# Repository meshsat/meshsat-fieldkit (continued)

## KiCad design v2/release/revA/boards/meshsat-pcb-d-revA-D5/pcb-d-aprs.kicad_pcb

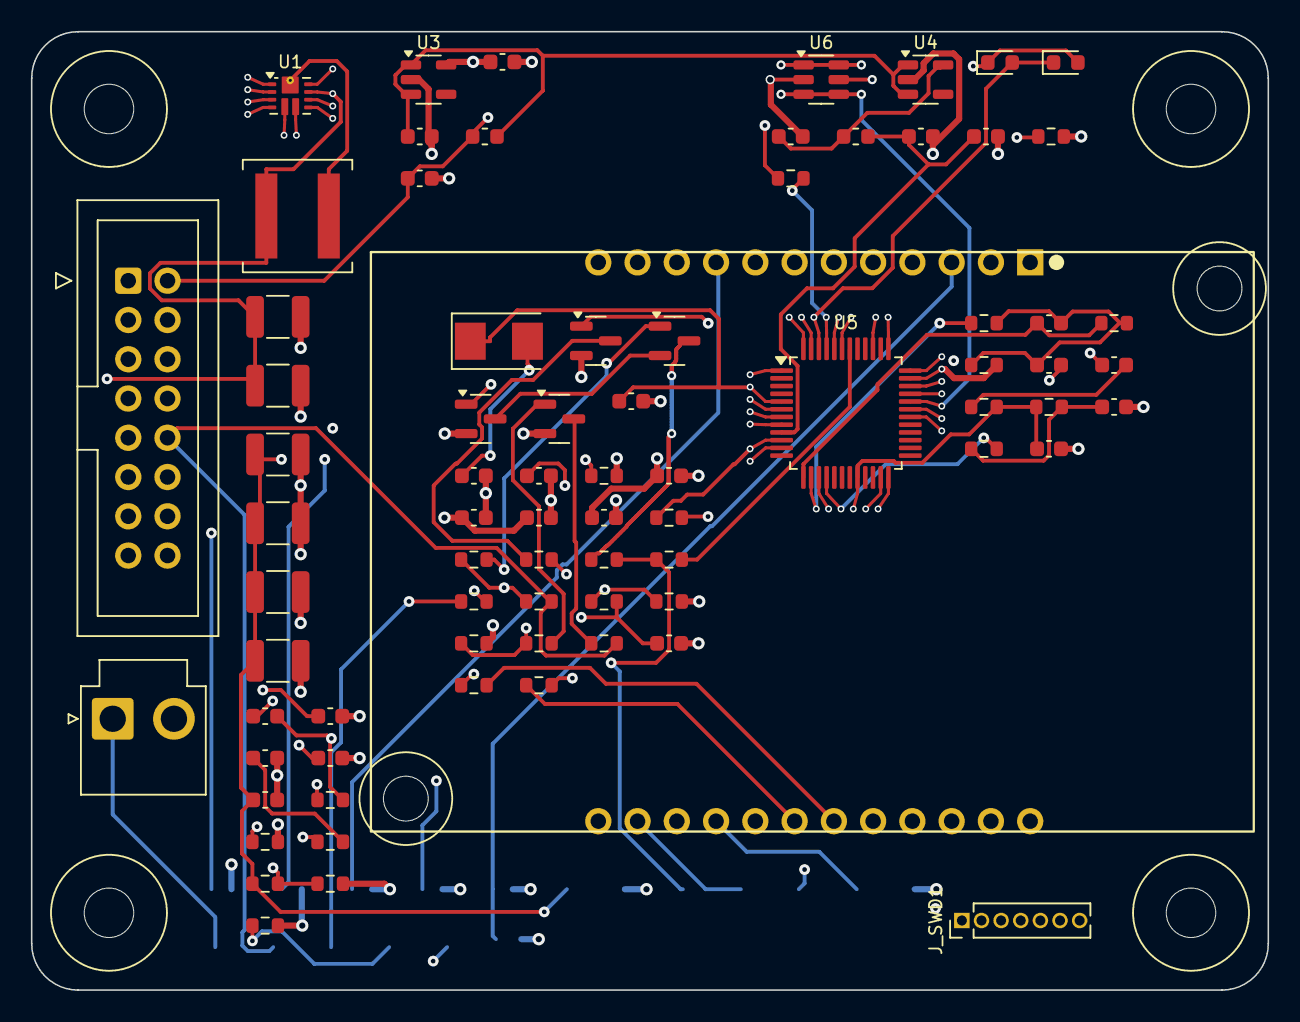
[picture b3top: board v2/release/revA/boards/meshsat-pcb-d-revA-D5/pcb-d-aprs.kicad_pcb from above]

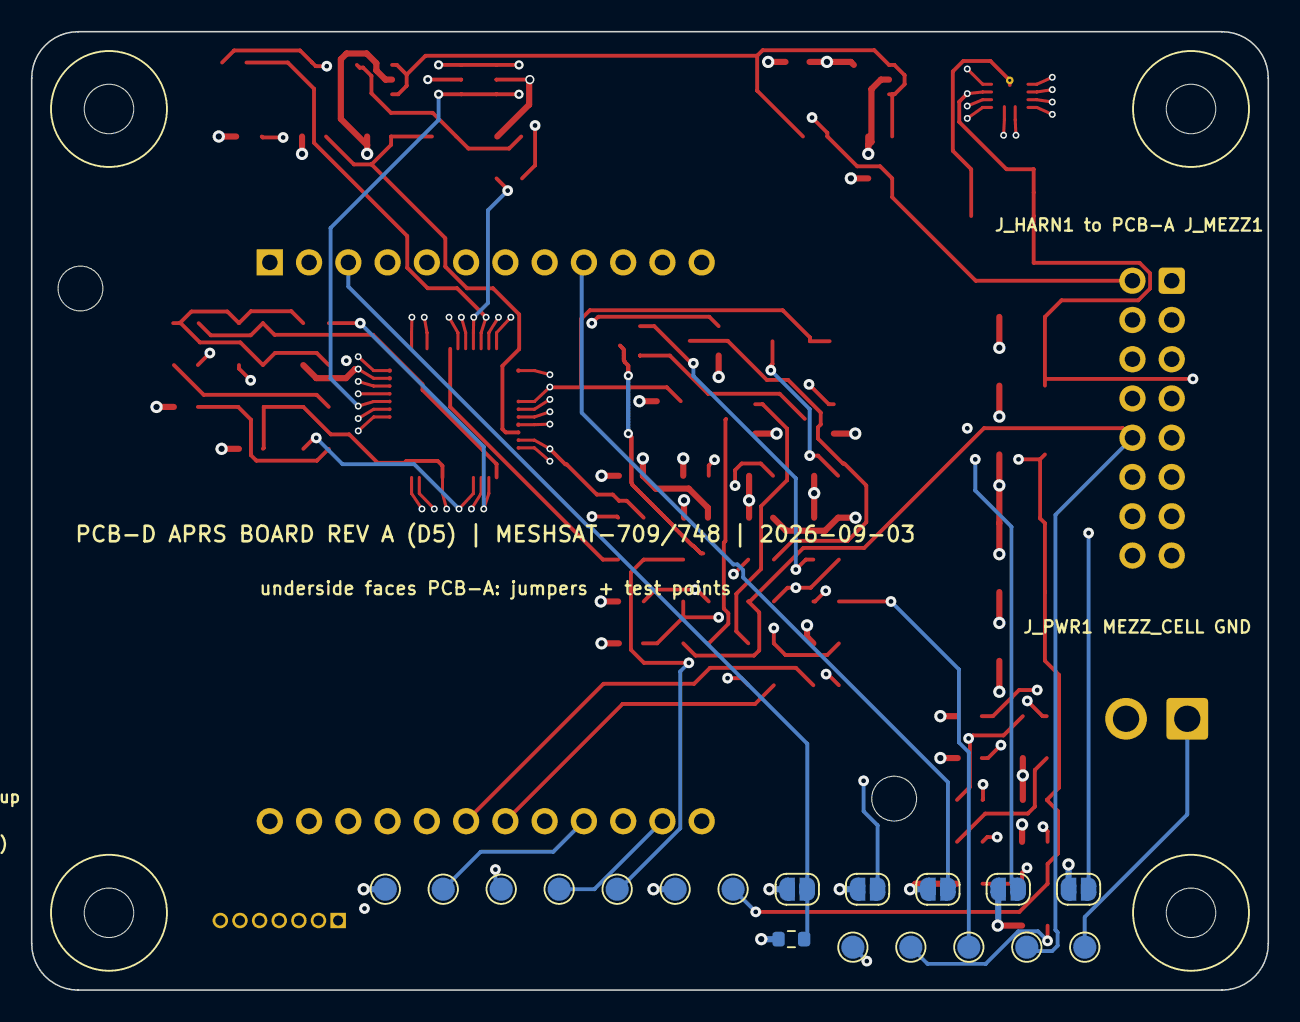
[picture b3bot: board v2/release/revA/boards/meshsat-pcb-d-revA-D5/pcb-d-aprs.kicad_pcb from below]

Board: 4 copper layers, 80.0 x 62.0 mm, 100 parts (18 on the bottom side), 64 nets.

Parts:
C1, C2: 22p NP0; C_0603_1608Metric
C4, C5, C6, C7, C10, C13, C14, C31: 4.7u; C_0603_1608Metric
C8, C9, C12, C15, C16, C17, C18, C25, C32: 100n; C_0603_1608Metric
C11: 4.7n NP0; C_0603_1608Metric
C20, C30: 100n 25V; C_0603_1608Metric
C21: 1u; C_0603_1608Metric
C22: 4.7n; C_0603_1608Metric
C23, C24: 22u 10V X7R 1210; C_1210_3225Metric
C26, C27, C28, C29: 22u 25V X7R 1210; C_1210_3225Metric
D1: green; LED_0603_1608Metric
D2: red; LED_0603_1608Metric
FB1, FB2: 600R@100MHz; L_0603_1608Metric
H1, H2, H3, H4: M3 standoff to PCB-A; MountingHole_3.2mm_M3
JP1: channel bit CH8 to GND (open = default); SolderJumper-2_P1.3mm_Open_RoundedPad1.0x1.5mm
JP2: channel bit CH4 to GND (open = default); SolderJumper-2_P1.3mm_Open_RoundedPad1.0x1.5mm
JP3: channel bit CH2 to GND (open = default); SolderJumper-2_P1.3mm_Open_RoundedPad1.0x1.5mm
JP4: channel bit CH1 to GND (open = default); SolderJumper-2_P1.3mm_Open_RoundedPad1.0x1.5mm
JP5: CS to GND = module sleep; SolderJumper-2_P1.3mm_Open_RoundedPad1.0x1.5mm
J_HARN1: harness to PCB-A J_MEZZ1 (IDC 2x8); UART pair and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; IDC-Header_2x08_P2.54mm_Vertical
J_PWR1: cell node from PCB-A J_MEZZ_PWR (JST-VH); JST_VH_B2P-VH_1x02_P3.96mm_Vertical
J_SWD1: SWD/DFU 1.27 mm: BOOT0 SWO NRST SWDIO GND SWCLK 3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; PinHeader_1x07_P1.27mm_Vertical
L1: 1.5uH XAL6030-152MEB (Isat 12 A, 5.6 mOhm); L_Coilcraft_XAL6030-XXX
Q1: BC847 (PTT2, spare); SOT-23
Q2: BC847 (PTT to the module); SOT-23
Q3: 2N7002 (EMCON inhibit in Q2 emitter); SOT-23
Q4: BC857 (TR mirror from RADIO_PTT); SOT-23
R1, R4, R10, R11, R18, R19: 1.5k; R_0603_1608Metric
R2: 4.7k; R_0603_1608Metric
R3, R8, R9, R15, R17, R41: 100R; R_0603_1608Metric
R5, R14, R16: 5.1k; R_0603_1608Metric
R12, R13: 22R; R_0603_1608Metric
R22: DNP 100R (mirror now via Q4); R_0603_1608Metric
R30: 301k 1% (500 kHz); R_0603_1608Metric
R31: 100k 1% (ILIM 10 A peak, 9 A min); R_0603_1608Metric
R32: 17.4k; R_0603_1608Metric
R33: 105k 1%; R_0603_1608Metric
R34: 20k 1%; R_0603_1608Metric
R35, R38, R39: 100k; R_0603_1608Metric
R36, R40: 10k; R_0603_1608Metric
R37: 1k; R_0603_1608Metric
TP1: V8; TestPoint_Pad_D1.5mm
TP2: GND; TestPoint_Pad_D1.5mm
TP3: RADIO_PTT; TestPoint_Pad_D1.5mm
TP4: RADIO_MIC; TestPoint_Pad_D1.5mm
TP5: RADIO_SPK; TestPoint_Pad_D1.5mm
TP6: SPKEN; TestPoint_Pad_D1.5mm
TP7: +3V3; TestPoint_Pad_D1.5mm
TP8: VIN_CELL; TestPoint_Pad_D1.5mm
TP9: TR_APRS; TestPoint_Pad_D1.5mm
TP10: RADIO_PTT2; TestPoint_Pad_D1.5mm
TP11: MEZZ_EN; TestPoint_Pad_D1.5mm
TP12: TX_INHIBIT_n; TestPoint_Pad_D1.5mm
U1: TPS61089 boost 7.6 V / 2 A; Texas_VQFN-RNR0011A-11
U2: DNP bench: DMR858M 5 W UHF module on 2 x 1x12 2.5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; DMR858M
U3: AP2112K-3.3 digital; SOT-23-5
U4: AP2112K-3.3 analog; SOT-23-5
U5: STM32F302CBT6 128 KB (AIOC firmware 1.4.1 is 128,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; LQFP-48_7x7mm_P0.5mm
U6: USBLC6-2SC6; SOT-23-6
Y1: 8MHz 20pF 5032; Crystal_SMD_5032-2Pin_5.0x3.2mm

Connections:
+3V3: C4.1, C7.1, C8.1, C17.1, C18.1, J_SWD1.7, Q4.2, R1.2, R36.2, R38.2, R39.2, TP7.1, U3.5, U5.1, U5.24, U5.36, U5.48
/+3.3VA: C9.1, C10.1, FB1.2, U5.9
/+5V_USB: C31.1, FB2.1, J_HARN1.2, U6.5
/ADC_BIAS: R3.2, U5.16
/AFIN: C11.1, R5.2, R16.1, U5.15, U5.20
/AFOUT: R2.1, U5.14
/BIAS_NODE: C16.1, R3.1, R16.2
/BOOT: C20.1, U1.10
/BOOT0: J_SWD1.1, R14.1, U5.44
/BST_VCC: C21.1, U1.2
/CH1: JP4.1, U2.10
/CH2: JP3.1, U2.9
/CH4: JP2.1, U2.8
/CH8: JP1.1, U2.7
/COMP: R32.1, U1.4
/COMPC: C22.1, R32.2
/CS: JP5.1, R36.1, U2.3
/DAC_ATTEN: C12.1, R17.1, U5.13
/FB8: R33.2, R34.1, U1.3
/FSW: R30.1, U1.1
/ILIM: R31.1, U1.8
/IN1: R19.2, U5.42
/IN2: R18.2, U5.43
/LDO_A: C5.1, FB1.1, U4.5
/LED_A: D1.2, D2.1, U5.46
/LED_K: D1.1, D2.2, R15.1
/LED_R: R15.2, U5.45
/MEZZ_EN: J_HARN1.11, R35.1, TP11.1, U1.7
/MIC_NODE: C12.2, C13.1, R2.2, R4.1, R17.2
/NRST: C15.1, J_SWD1.3, U5.7
/OSCIN: C1.1, U5.5, Y1.1
/OSCOUT: C2.1, U5.6, Y1.2
/OUT1: R11.1, R22.1, U5.11
/OUT2: R10.1, U5.10
/Q1_B: Q1.1, R10.2
/Q1_C: Q1.3, R12.1
/Q2_B: Q2.1, R11.2
/Q2_C: Q2.3, R13.1
/Q2_E: Q2.2, Q3.3
/Q3_G: C32.1, Q3.1, R37.2
/Q4_B: Q4.1, R40.2
/Q4_C: Q4.3, R41.1
/RADIO_MIC: C13.2, TP4.1, U2.14
/RADIO_PTT: R13.2, R19.1, R39.1, R40.1, TP3.1, U2.5
/RADIO_PTT2: R12.2, R18.1, TP10.1
/RADIO_RX: R8.2, U2.19
/RADIO_SPK: C14.1, TP5.1, U2.6
/RADIO_TX: R9.1, U2.18
/SPKEN: J_HARN1.14, TP6.1, U2.16
/SPK_NODE: C14.2, R5.1
/SW: C20.2, L1.2, R30.2, U1.11
/SWCLK: J_SWD1.6, U5.37
/SWDIO: J_SWD1.4, U5.34
/SWO: J_SWD1.2, U5.39
/TR_APRS: J_HARN1.10, R22.2, R41.2, TP9.1
/TX_INHIBIT_n: J_HARN1.15, R37.1, R38.1, TP12.1
/USART_RX: R9.2, U5.31
/USART_TX: R8.1, U5.30
/USB_DM: J_HARN1.4, U5.32, U6.3, U6.4
/USB_DP: J_HARN1.3, R1.1, U5.33, U6.1, U6.6
/V8: C26.1, C27.1, C28.1, C29.1, C30.1, R33.1, TP1.1, U1.6, U2.1
/VIN_CELL: C23.1, C24.1, C25.1, J_PWR1.1, L1.1, TP8.1, U1.9
/VIN_LDO: C6.1, FB2.2, U3.1, U3.3, U4.1, U4.3
GND: C1.2, C2.2, C4.2, C5.2, C6.2, C7.2, C8.2, C9.2, C10.2, C11.2, C15.2, C16.2, C17.2, C18.2, C21.2, C22.2, C23.2, C24.2, C25.2, C26.2, C27.2, C28.2, C29.2, C30.2, C31.2, C32.2, JP1.2, JP2.2, JP3.2, JP4.2, JP5.2, J_HARN1.1, J_HARN1.5, J_HARN1.9, J_HARN1.13, J_HARN1.16, J_PWR1.2, J_SWD1.5, Q1.2, Q3.2, R4.2, R14.2, R31.2, R34.2, R35.2, TP2.1, U1.5, U2.2, U2.4, U2.13, U2.15, U2.17, U3.2, U4.2, U5.8, U5.23, U5.35, U5.47, U6.2

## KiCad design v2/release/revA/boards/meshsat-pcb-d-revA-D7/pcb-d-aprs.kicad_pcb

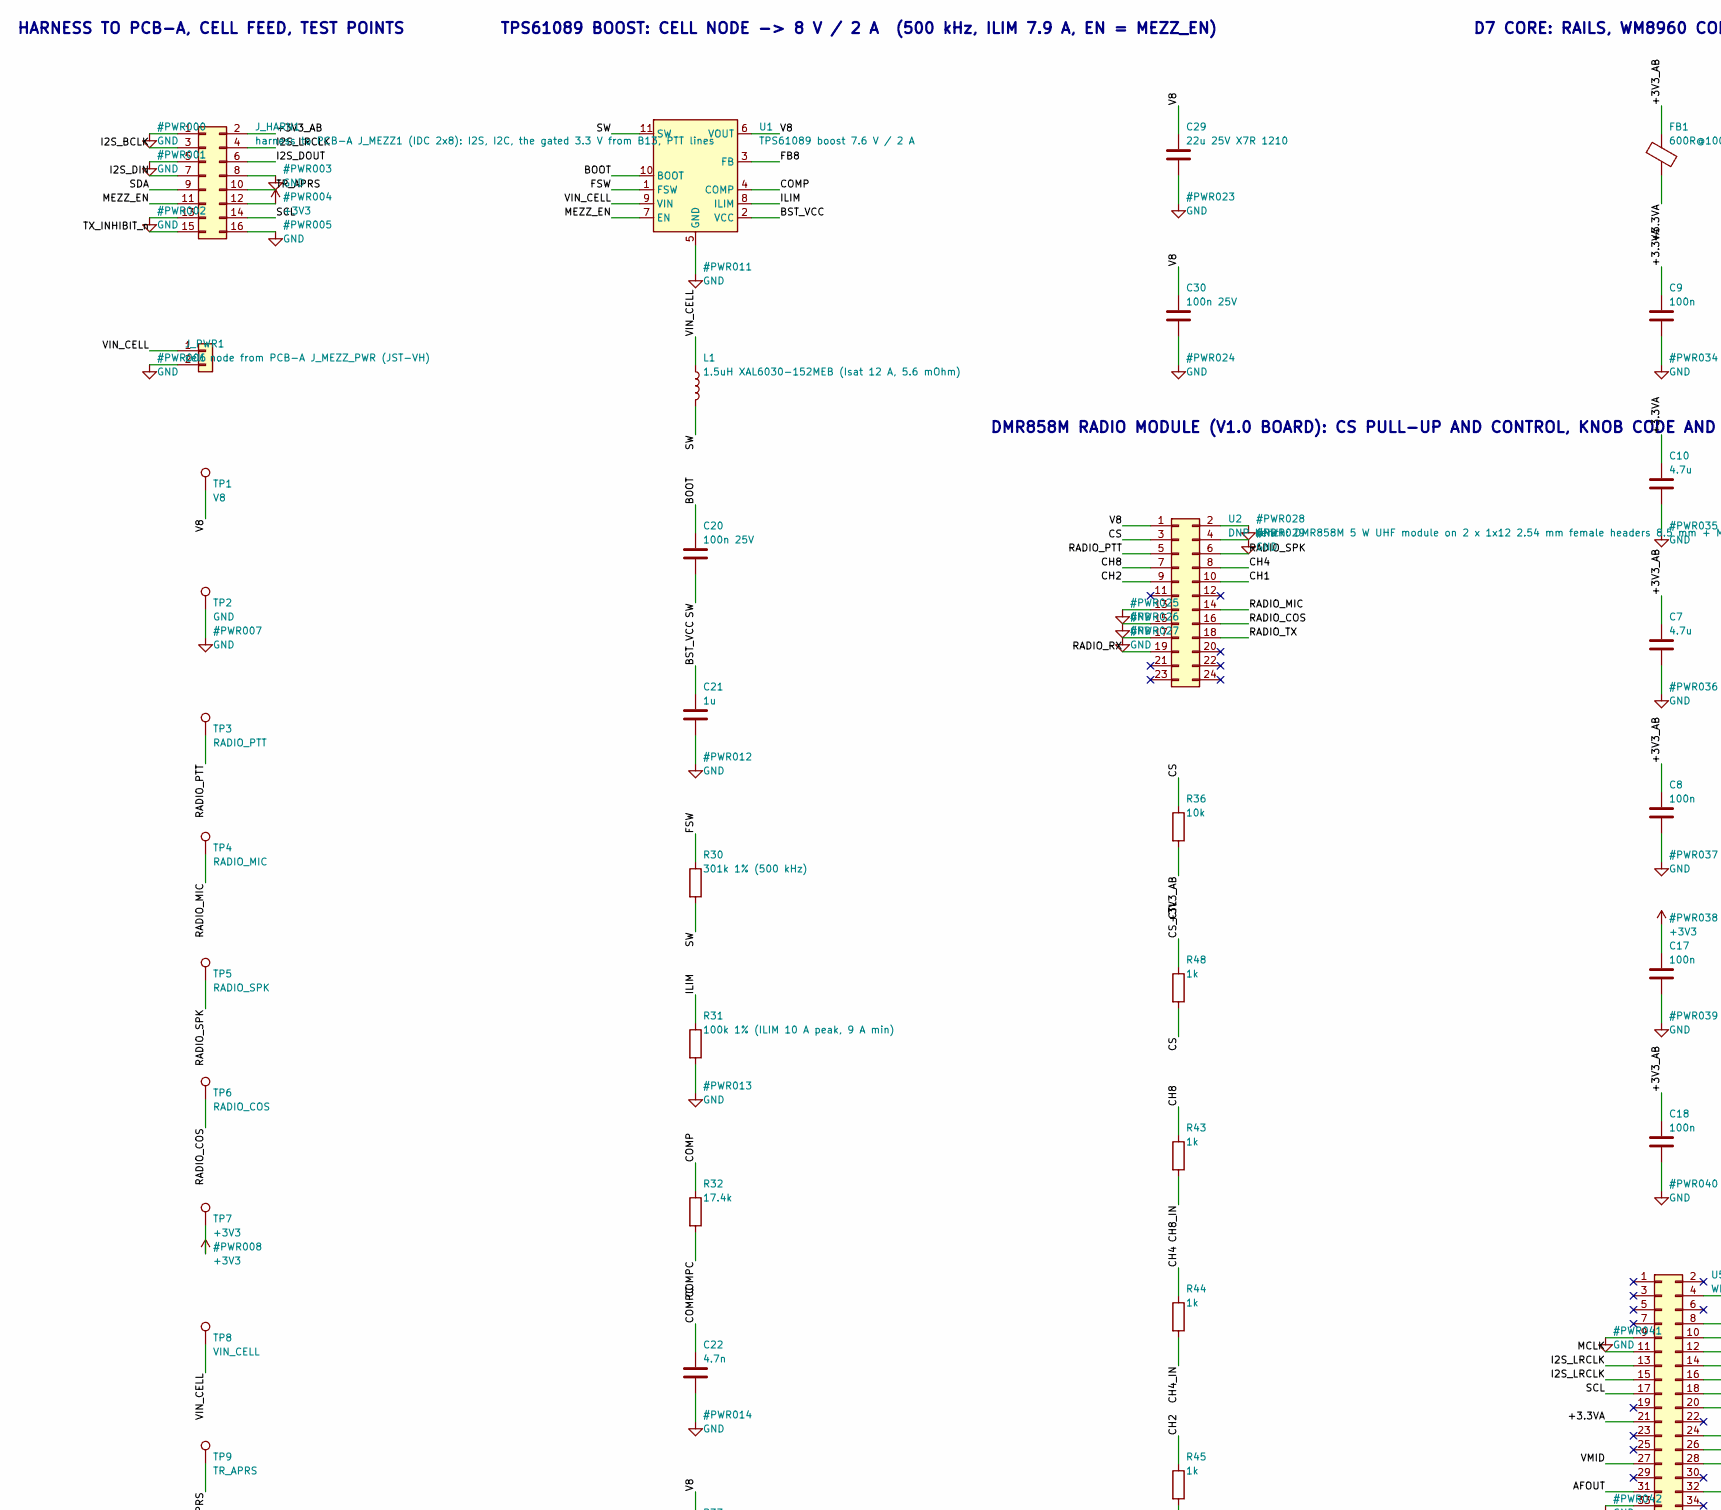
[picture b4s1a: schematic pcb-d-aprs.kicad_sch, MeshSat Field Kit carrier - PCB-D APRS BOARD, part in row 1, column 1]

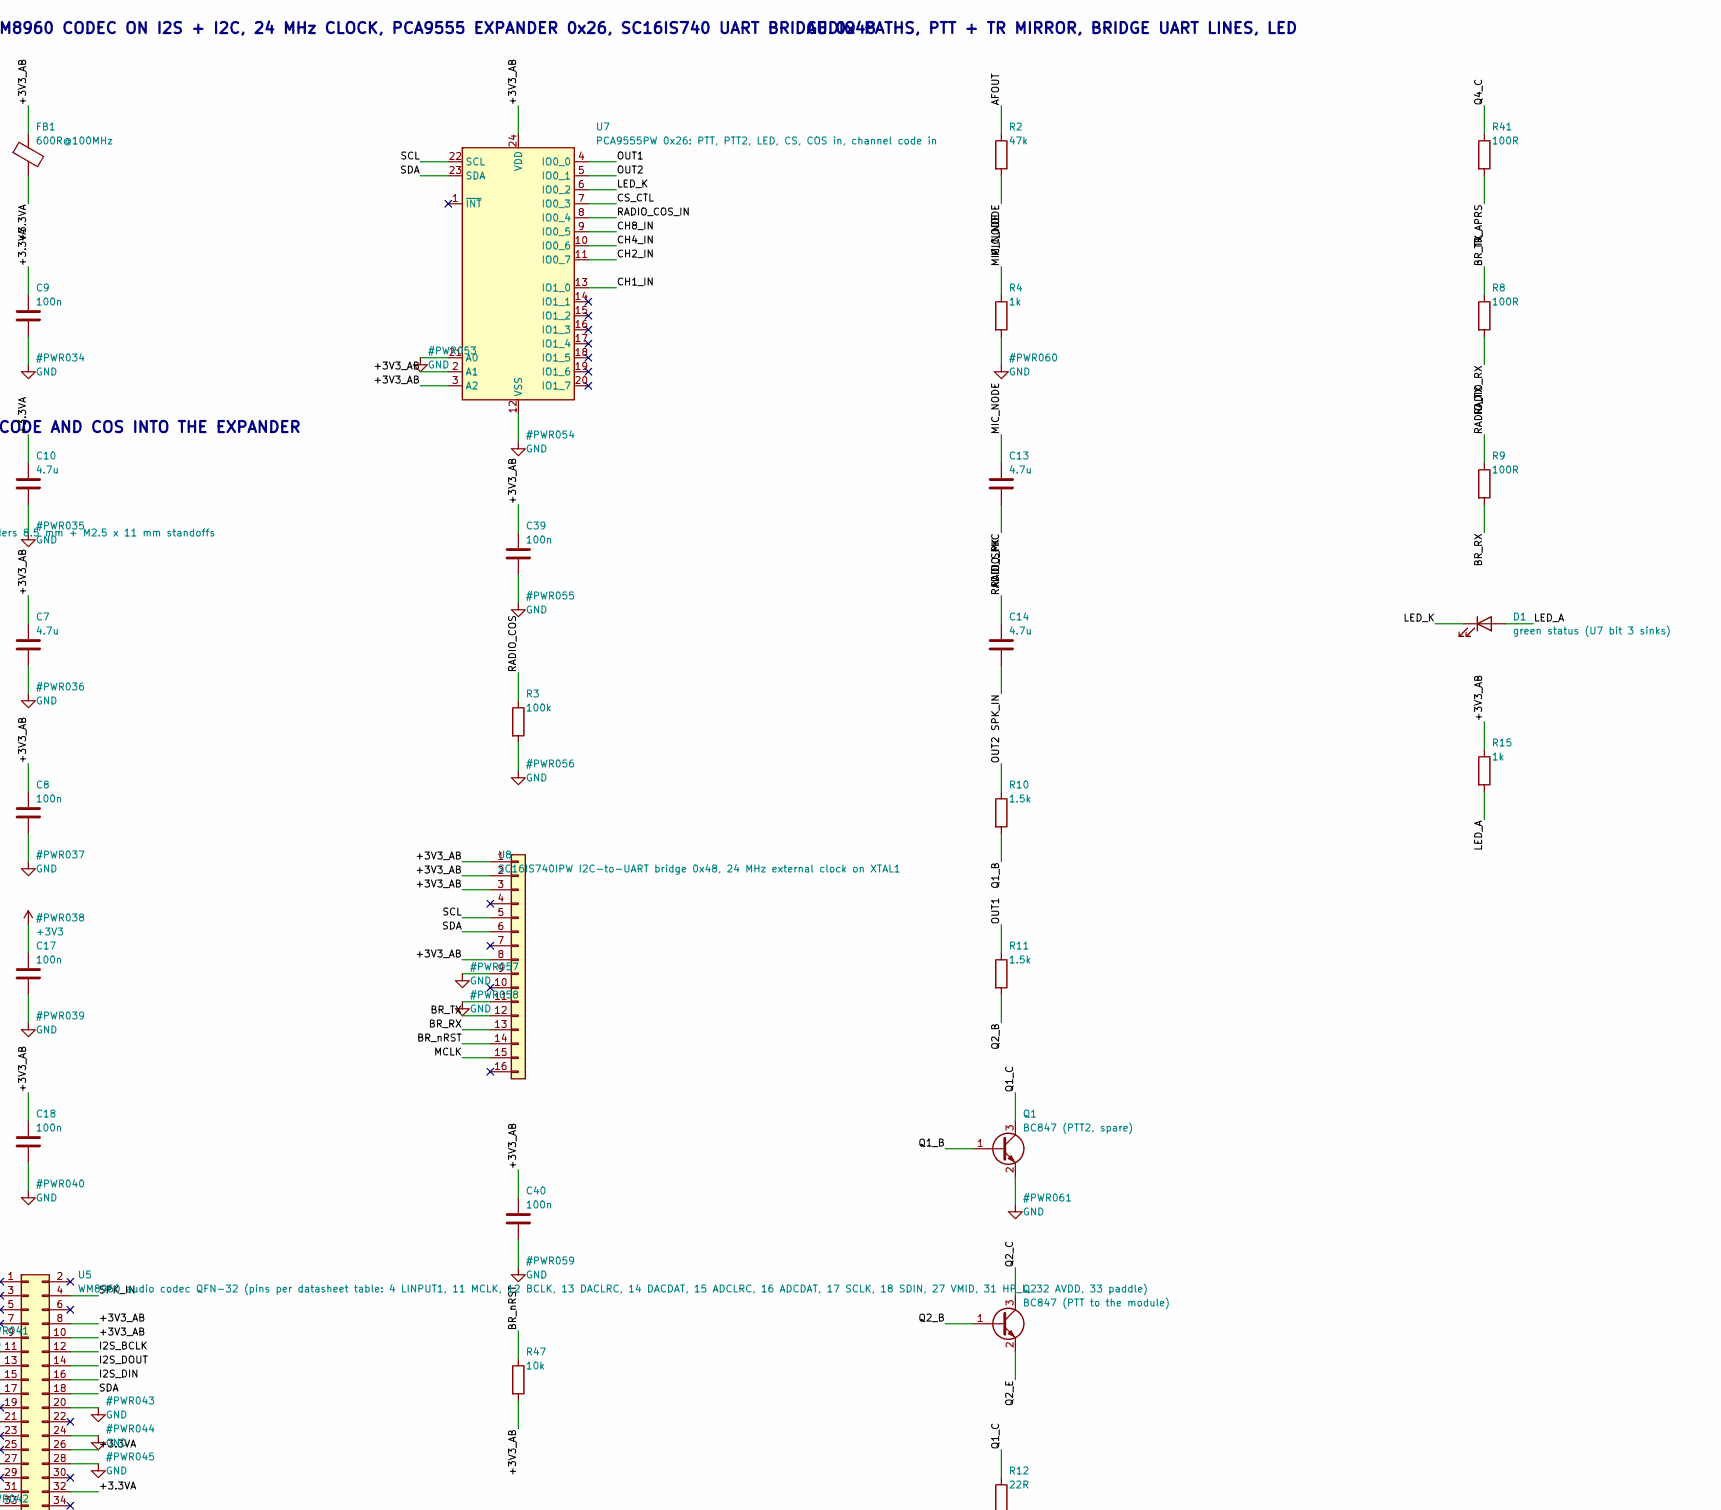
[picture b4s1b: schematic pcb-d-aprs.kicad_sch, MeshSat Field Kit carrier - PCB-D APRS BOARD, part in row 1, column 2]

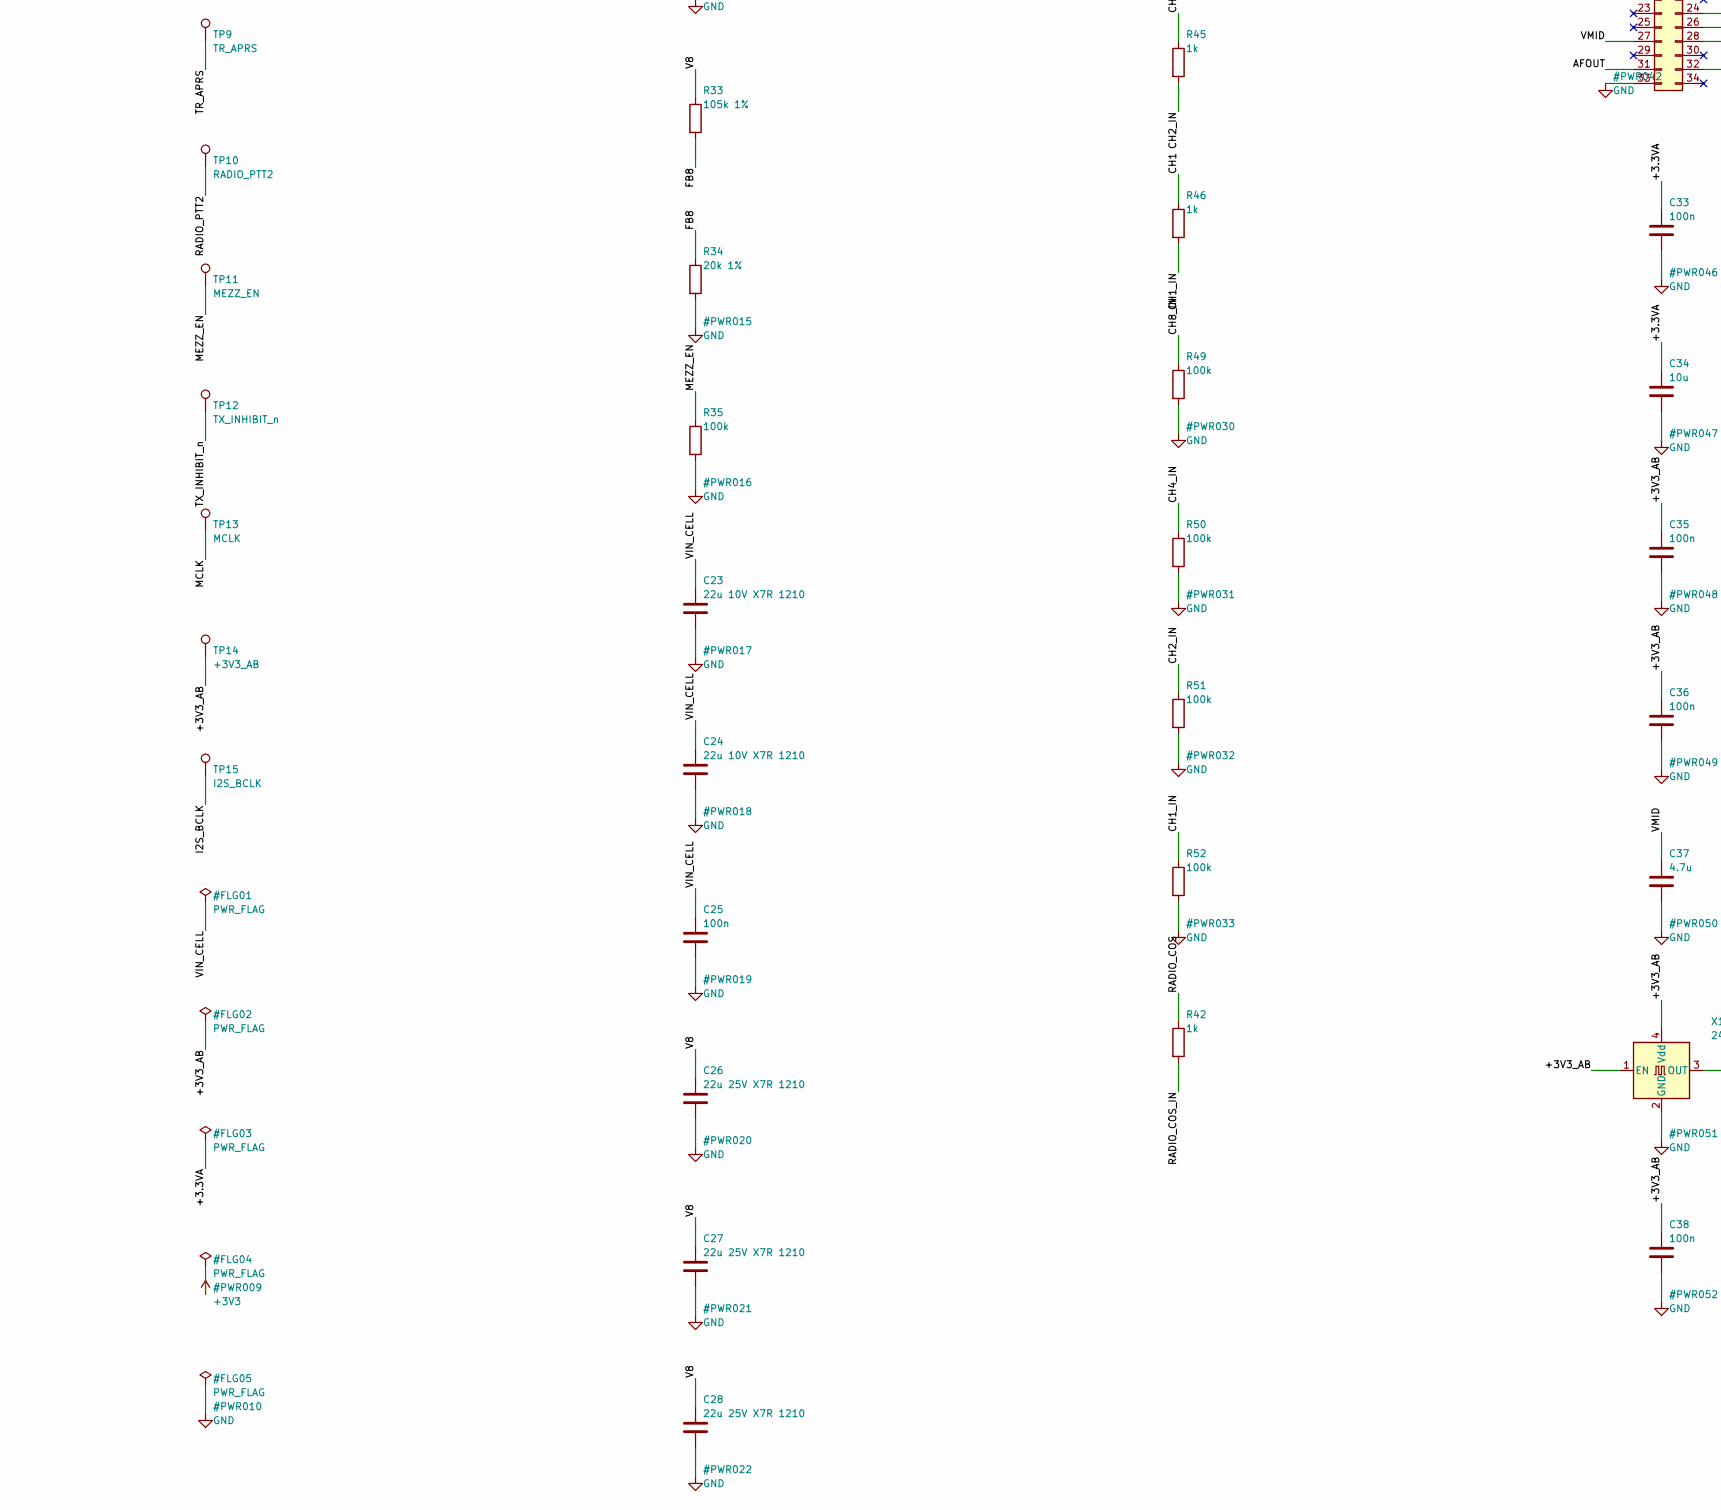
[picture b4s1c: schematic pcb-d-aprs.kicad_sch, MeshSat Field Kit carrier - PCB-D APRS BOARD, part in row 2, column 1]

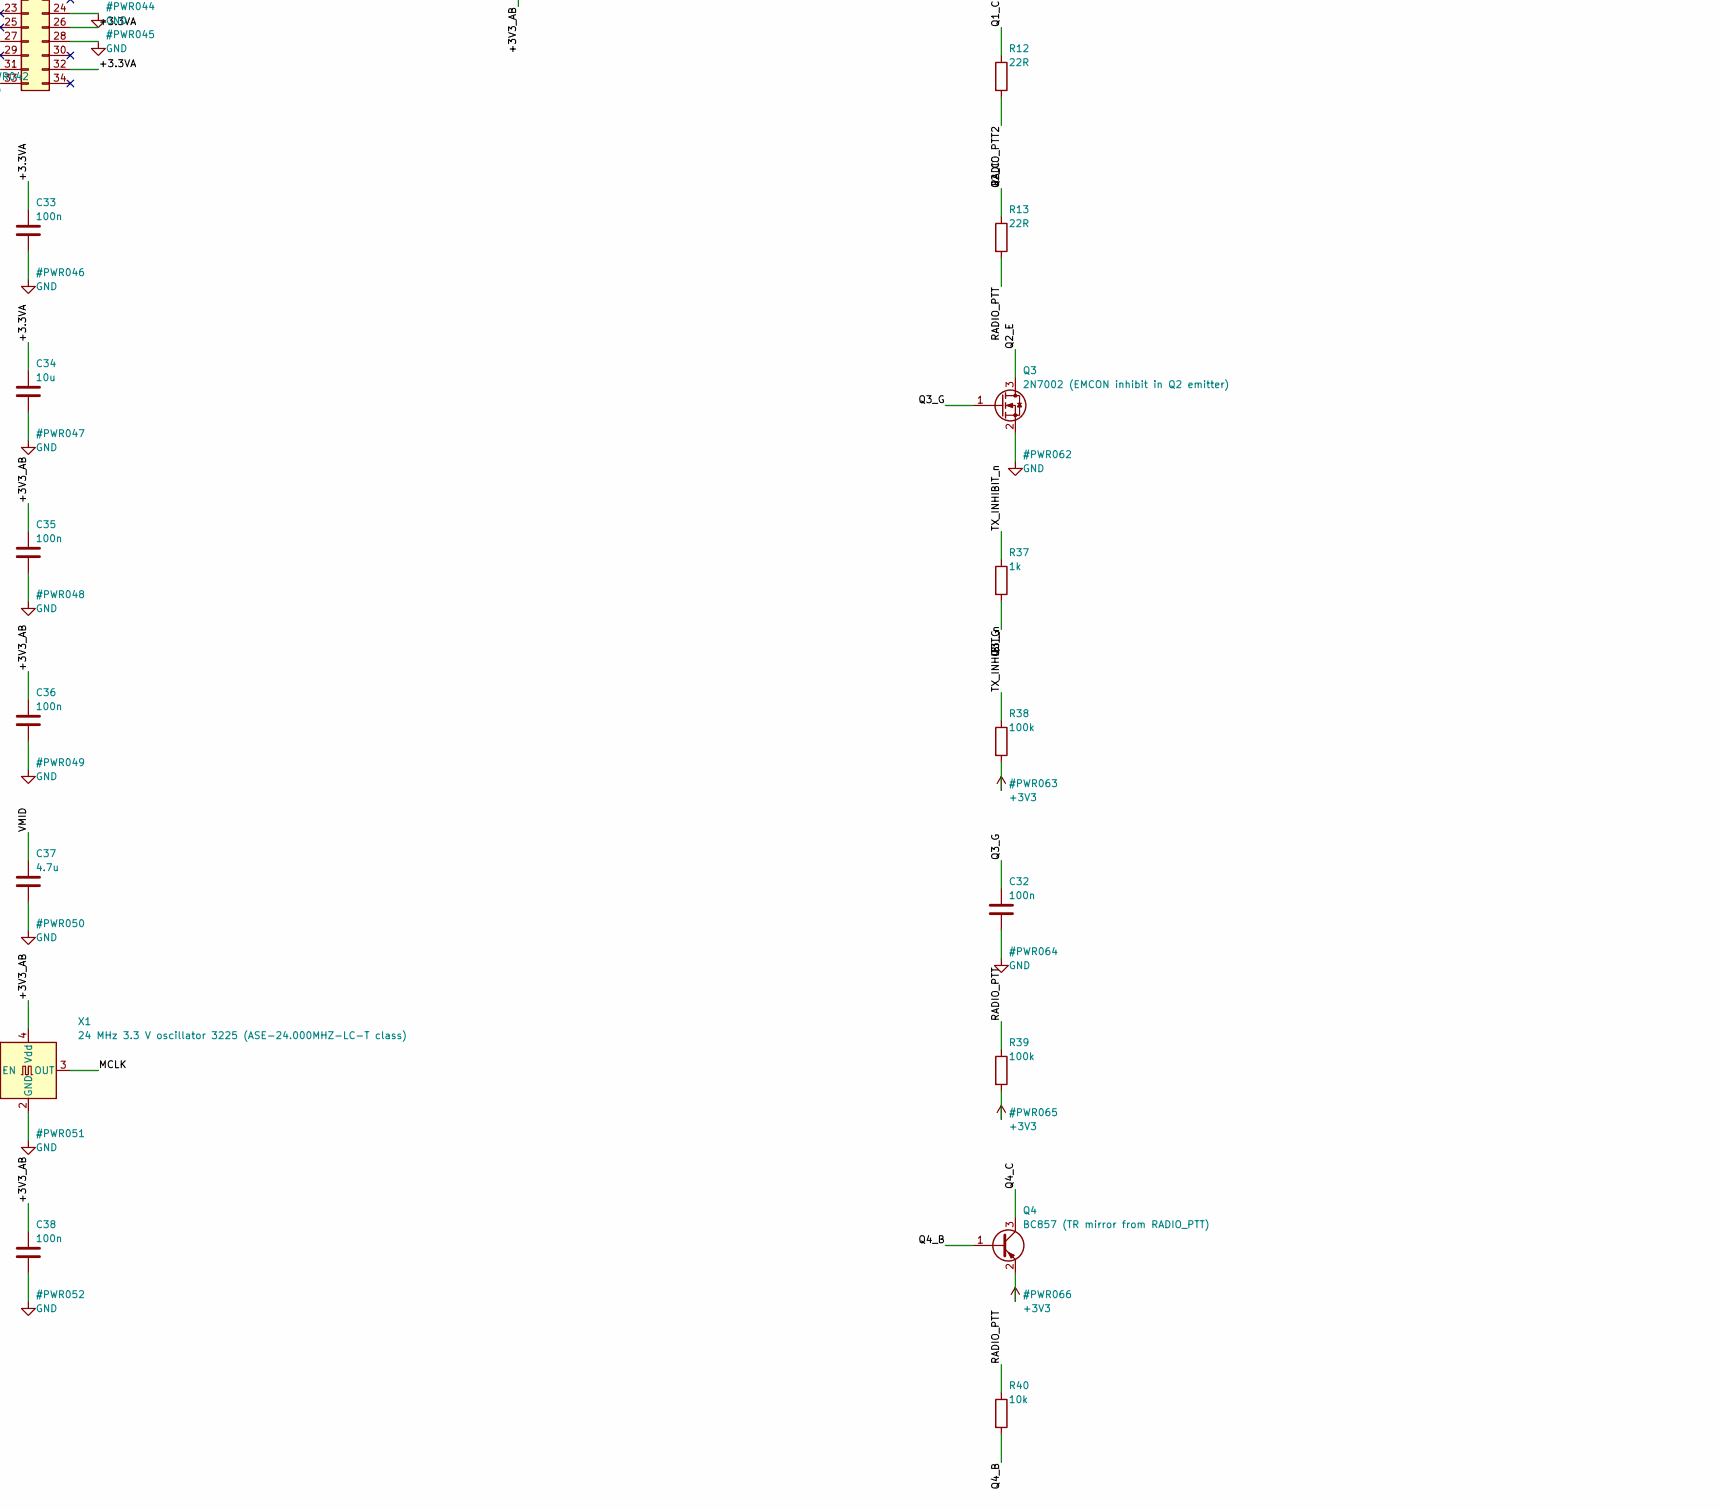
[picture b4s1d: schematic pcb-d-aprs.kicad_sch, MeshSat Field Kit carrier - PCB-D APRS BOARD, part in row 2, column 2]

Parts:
C7, C10, C13, C14, C37: 4.7u; C_0603_1608Metric
C8, C9, C17, C18, C25, C32, C33, C35, C36, C38, C39, C40: 100n; C_0603_1608Metric
C20, C30: 100n 25V; C_0603_1608Metric
C21: 1u; C_0603_1608Metric
C22: 4.7n; C_0603_1608Metric
C23, C24: 22u 10V X7R 1210; C_1210_3225Metric
C26, C27, C28, C29: 22u 25V X7R 1210; C_1210_3225Metric
C34: 10u; C_1210_3225Metric
D1: green status (U7 bit 3 sinks); LED_0603_1608Metric; LCSC C72043
FB1: 600R@100MHz; L_0603_1608Metric
J_HARN1: harness to PCB-A J_MEZZ1 (IDC 2x8): I2S, I2C, the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; IDC-Header_2x08_P2.54mm_Vertical
J_PWR1: cell node from PCB-A J_MEZZ_PWR (JST-VH); JST_VH_B2P-VH_1x02_P3.96mm_Vertical
L1: 1.5uH XAL6030-152MEB (Isat 12 A, 5.6 mOhm); L_Coilcraft_XAL6030-XXX
Q1: BC847 (PTT2, spare); SOT-23
Q2: BC847 (PTT to the module); SOT-23
Q3: 2N7002 (EMCON inhibit in Q2 emitter); SOT-23
Q4: BC857 (TR mirror from RADIO_PTT); SOT-23
R2: 47k; R_0603_1608Metric
R3, R35, R38, R39, R49, R50, R51, R52: 100k; R_0603_1608Metric
R4, R15, R37, R42, R43, R44, R45, R46, R48: 1k; R_0603_1608Metric
R8, R9, R41: 100R; R_0603_1608Metric
R10, R11: 1.5k; R_0603_1608Metric
R12, R13: 22R; R_0603_1608Metric
R30: 301k 1% (500 kHz); R_0603_1608Metric
R31: 100k 1% (ILIM 10 A peak, 9 A min); R_0603_1608Metric
R32: 17.4k; R_0603_1608Metric
R33: 105k 1%; R_0603_1608Metric
R34: 20k 1%; R_0603_1608Metric
R36, R40, R47: 10k; R_0603_1608Metric
TP1: V8; TestPoint_Pad_D1.5mm
TP2: GND; TestPoint_Pad_D1.5mm
TP3: RADIO_PTT; TestPoint_Pad_D1.5mm
TP4: RADIO_MIC; TestPoint_Pad_D1.5mm
TP5: RADIO_SPK; TestPoint_Pad_D1.5mm
TP6: RADIO_COS; TestPoint_Pad_D1.5mm
TP7: +3V3; TestPoint_Pad_D1.5mm
TP8: VIN_CELL; TestPoint_Pad_D1.5mm
TP9: TR_APRS; TestPoint_Pad_D1.5mm
TP10: RADIO_PTT2; TestPoint_Pad_D1.5mm
TP11: MEZZ_EN; TestPoint_Pad_D1.5mm
TP12: TX_INHIBIT_n; TestPoint_Pad_D1.5mm
TP13: MCLK; TestPoint_Pad_D1.5mm
TP14: +3V3_AB; TestPoint_Pad_D1.5mm
TP15: I2S_BCLK; TestPoint_Pad_D1.5mm
U1: TPS61089 boost 7.6 V / 2 A; Texas_VQFN-RNR0011A-11
U2: DNP bench: DMR858M 5 W UHF module on 2 x 1x12 2.5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; DMR858M
U5: WM8960 audio codec QFN-32 (pins per datasheet tab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; QFN-32-1EP_5x5mm_P0.5mm_EP3.1x3.1mm
U7: PCA9555PW 0x26: PTT, PTT2, LED, CS, COS in, chann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; TSSOP-24_4.4x7.8mm_P0.65mm; LCSC C5626
U8: SC16IS740IPW I2C-to-UART bridge 0x48, 24 MHz exte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; TSSOP-16_4.4x5mm_P0.65mm
X1: 24 MHz 3.3 V oscillator 3225 (ASE-24.000MHZ-LC-T 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; Oscillator_SMD_Abracon_ASE-4Pin_3.2x2.5mm

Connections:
+3V3: C17.1, J_HARN1.12, Q4.2 (E), R38.2, R39.2, TP7.1
/+3.3VA: C9.1, C10.1, C33.1, C34.1, FB1.2, U5.21, U5.26, U5.32
/+3V3_AB: C7.1, C8.1, C18.1, C35.1, C36.1, C38.1, C39.1, C40.1, FB1.1, J_HARN1.2, R15.1, R36.2, R47.2, TP14.1, U5.8, U5.10, U7.2 (A1), U7.3 (A2), U7.24 (VDD), U8.1, U8.2, U8.3, U8.8, X1.1 (EN), X1.4 (Vdd)
/AFOUT: R2.1, U5.31
/BOOT: C20.1, U1.10 (BOOT)
/BR_RX: R9.2, U8.13
/BR_TX: R8.1, U8.12
/BR_nRST: R47.1, U8.14
/BST_VCC: C21.1, U1.2 (VCC)
/CH1: R46.1, U2.10
/CH1_IN: R46.2, R52.1, U7.13 (IO1_0)
/CH2: R45.1, U2.9
/CH2_IN: R45.2, R51.1, U7.11 (IO0_7)
/CH4: R44.1, U2.8
/CH4_IN: R44.2, R50.1, U7.10 (IO0_6)
/CH8: R43.1, U2.7
/CH8_IN: R43.2, R49.1, U7.9 (IO0_5)
/COMP: R32.1, U1.4 (COMP)
/COMPC: C22.1, R32.2
/CS: R36.1, R48.2, U2.3
/CS_CTL: R48.1, U7.7 (IO0_3)
/FB8: R33.2, R34.1, U1.3 (FB)
/FSW: R30.1, U1.1 (FSW)
/I2S_BCLK: J_HARN1.3, TP15.1, U5.12
/I2S_DIN: J_HARN1.7, U5.16
/I2S_DOUT: J_HARN1.6, U5.14
/I2S_LRCLK: J_HARN1.4, U5.13, U5.15
/ILIM: R31.1, U1.8 (ILIM)
/LED_A: D1.2 (A), R15.2
/LED_K: D1.1 (K), U7.6 (IO0_2)
/MCLK: TP13.1, U5.11, U8.15, X1.3 (OUT)
/MEZZ_EN: J_HARN1.11, R35.1, TP11.1, U1.7 (EN)
/MIC_NODE: C13.1, R2.2, R4.1
/OUT1: R11.1, U7.4 (IO0_0)
/OUT2: R10.1, U7.5 (IO0_1)
/Q1_B: Q1.1 (B), R10.2
/Q1_C: Q1.3 (C), R12.1
/Q2_B: Q2.1 (B), R11.2
/Q2_C: Q2.3 (C), R13.1
/Q2_E: Q2.2 (E), Q3.3 (D)
/Q3_G: C32.1, Q3.1 (G), R37.2
/Q4_B: Q4.1 (B), R40.2
/Q4_C: Q4.3 (C), R41.1
/RADIO_COS: R3.1, R42.1, TP6.1, U2.16
/RADIO_COS_IN: R42.2, U7.8 (IO0_4)
/RADIO_MIC: C13.2, TP4.1, U2.14
/RADIO_PTT: R13.2, R39.1, R40.1, TP3.1, U2.5
/RADIO_PTT2: R12.2, TP10.1
/RADIO_RX: R8.2, U2.19
/RADIO_SPK: C14.1, TP5.1, U2.6
/RADIO_TX: R9.1, U2.18
/SCL: J_HARN1.14, U5.17, U7.22 (SCL), U8.5
/SDA: J_HARN1.9, U5.18, U7.23 (SDA), U8.6
/SPK_IN: C14.2, U5.4
/SW: C20.2, L1.2, R30.2, U1.11 (SW)
/TR_APRS: J_HARN1.10, R41.2, TP9.1
/TX_INHIBIT_n: J_HARN1.15, R37.1, R38.1, TP12.1
/V8: C26.1, C27.1, C28.1, C29.1, C30.1, R33.1, TP1.1, U1.6 (VOUT), U2.1
/VIN_CELL: C23.1, C24.1, C25.1, J_PWR1.1, L1.1, TP8.1, U1.9 (VIN)
/VMID: C37.1, U5.27
GND: C7.2, C8.2, C9.2, C10.2, C17.2, C18.2, C21.2, C22.2, C23.2, C24.2, C25.2, C26.2, C27.2, C28.2, C29.2, C30.2, C32.2, C33.2, C34.2, C35.2, C36.2, C37.2, C38.2, C39.2, C40.2, J_HARN1.1, J_HARN1.5, J_HARN1.8, J_HARN1.13, J_HARN1.16, J_PWR1.2, Q1.2 (E), Q3.2 (S), R3.2, R4.2, R31.2, R34.2, R35.2, R49.2, R50.2, R51.2, R52.2, TP2.1, U1.5 (GND), U2.2, U2.4, U2.13, U2.15, U2.17, U5.9, U5.20, U5.24, U5.28, U5.33, U7.12 (VSS), U7.21 (A0), U8.9, U8.11, X1.2 (GND)

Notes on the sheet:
HARNESS TO PCB-A, CELL FEED, TEST POINTS
TPS61089 BOOST: CELL NODE -> 8 V / 2 A (500 kHz, ILIM 7.9 A, EN = MEZZ_EN)
DMR858M RADIO MODULE (V1.0 BOARD): CS PULL-UP AND CONTROL, KNOB CODE AND COS INTO THE EXPANDER
D7 CORE: RAILS, WM8960 CODEC ON I2S + I2C, 24 MHz CLOCK, PCA9555 EXPANDER 0x26, SC16IS740 UART BRIDGE 0x48
AUDIO PATHS, PTT + TR MIRROR, BRIDGE UART LINES, LED

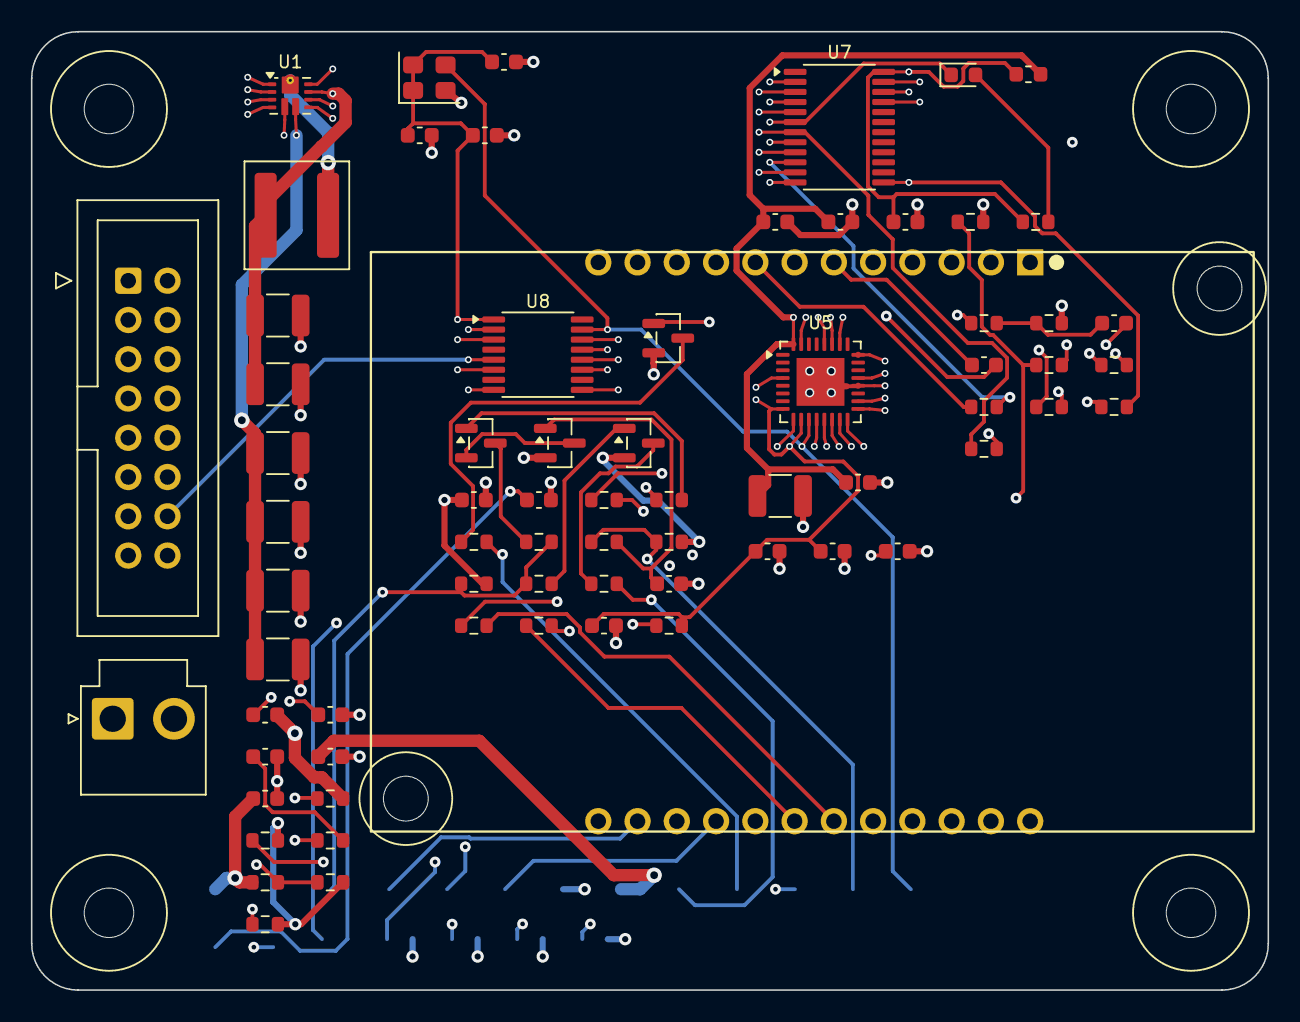
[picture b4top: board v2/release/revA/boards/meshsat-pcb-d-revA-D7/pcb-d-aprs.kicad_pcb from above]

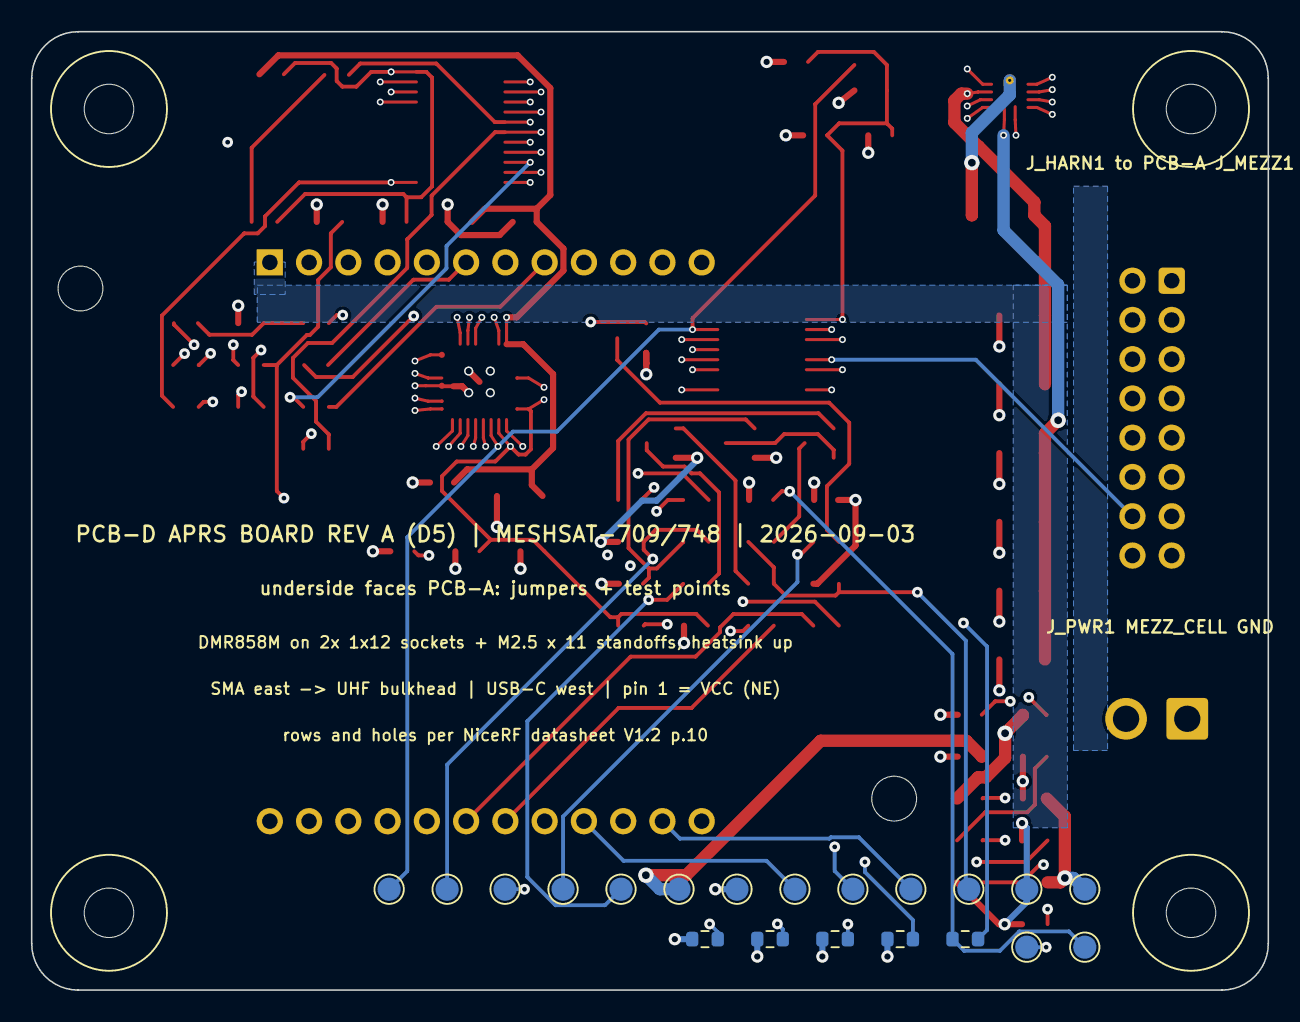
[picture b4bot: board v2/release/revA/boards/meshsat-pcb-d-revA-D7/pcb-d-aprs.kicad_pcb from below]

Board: 4 copper layers, 80.0 x 62.0 mm, 95 parts (20 on the bottom side), 61 nets.

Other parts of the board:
H1, H2, H3, H4: M3 standoff to PCB-A; MountingHole_3.2mm_M3
